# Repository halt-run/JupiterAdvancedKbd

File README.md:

# JupiterAdvancedKbd
Rep for the Jupiter Advanced Keyboard

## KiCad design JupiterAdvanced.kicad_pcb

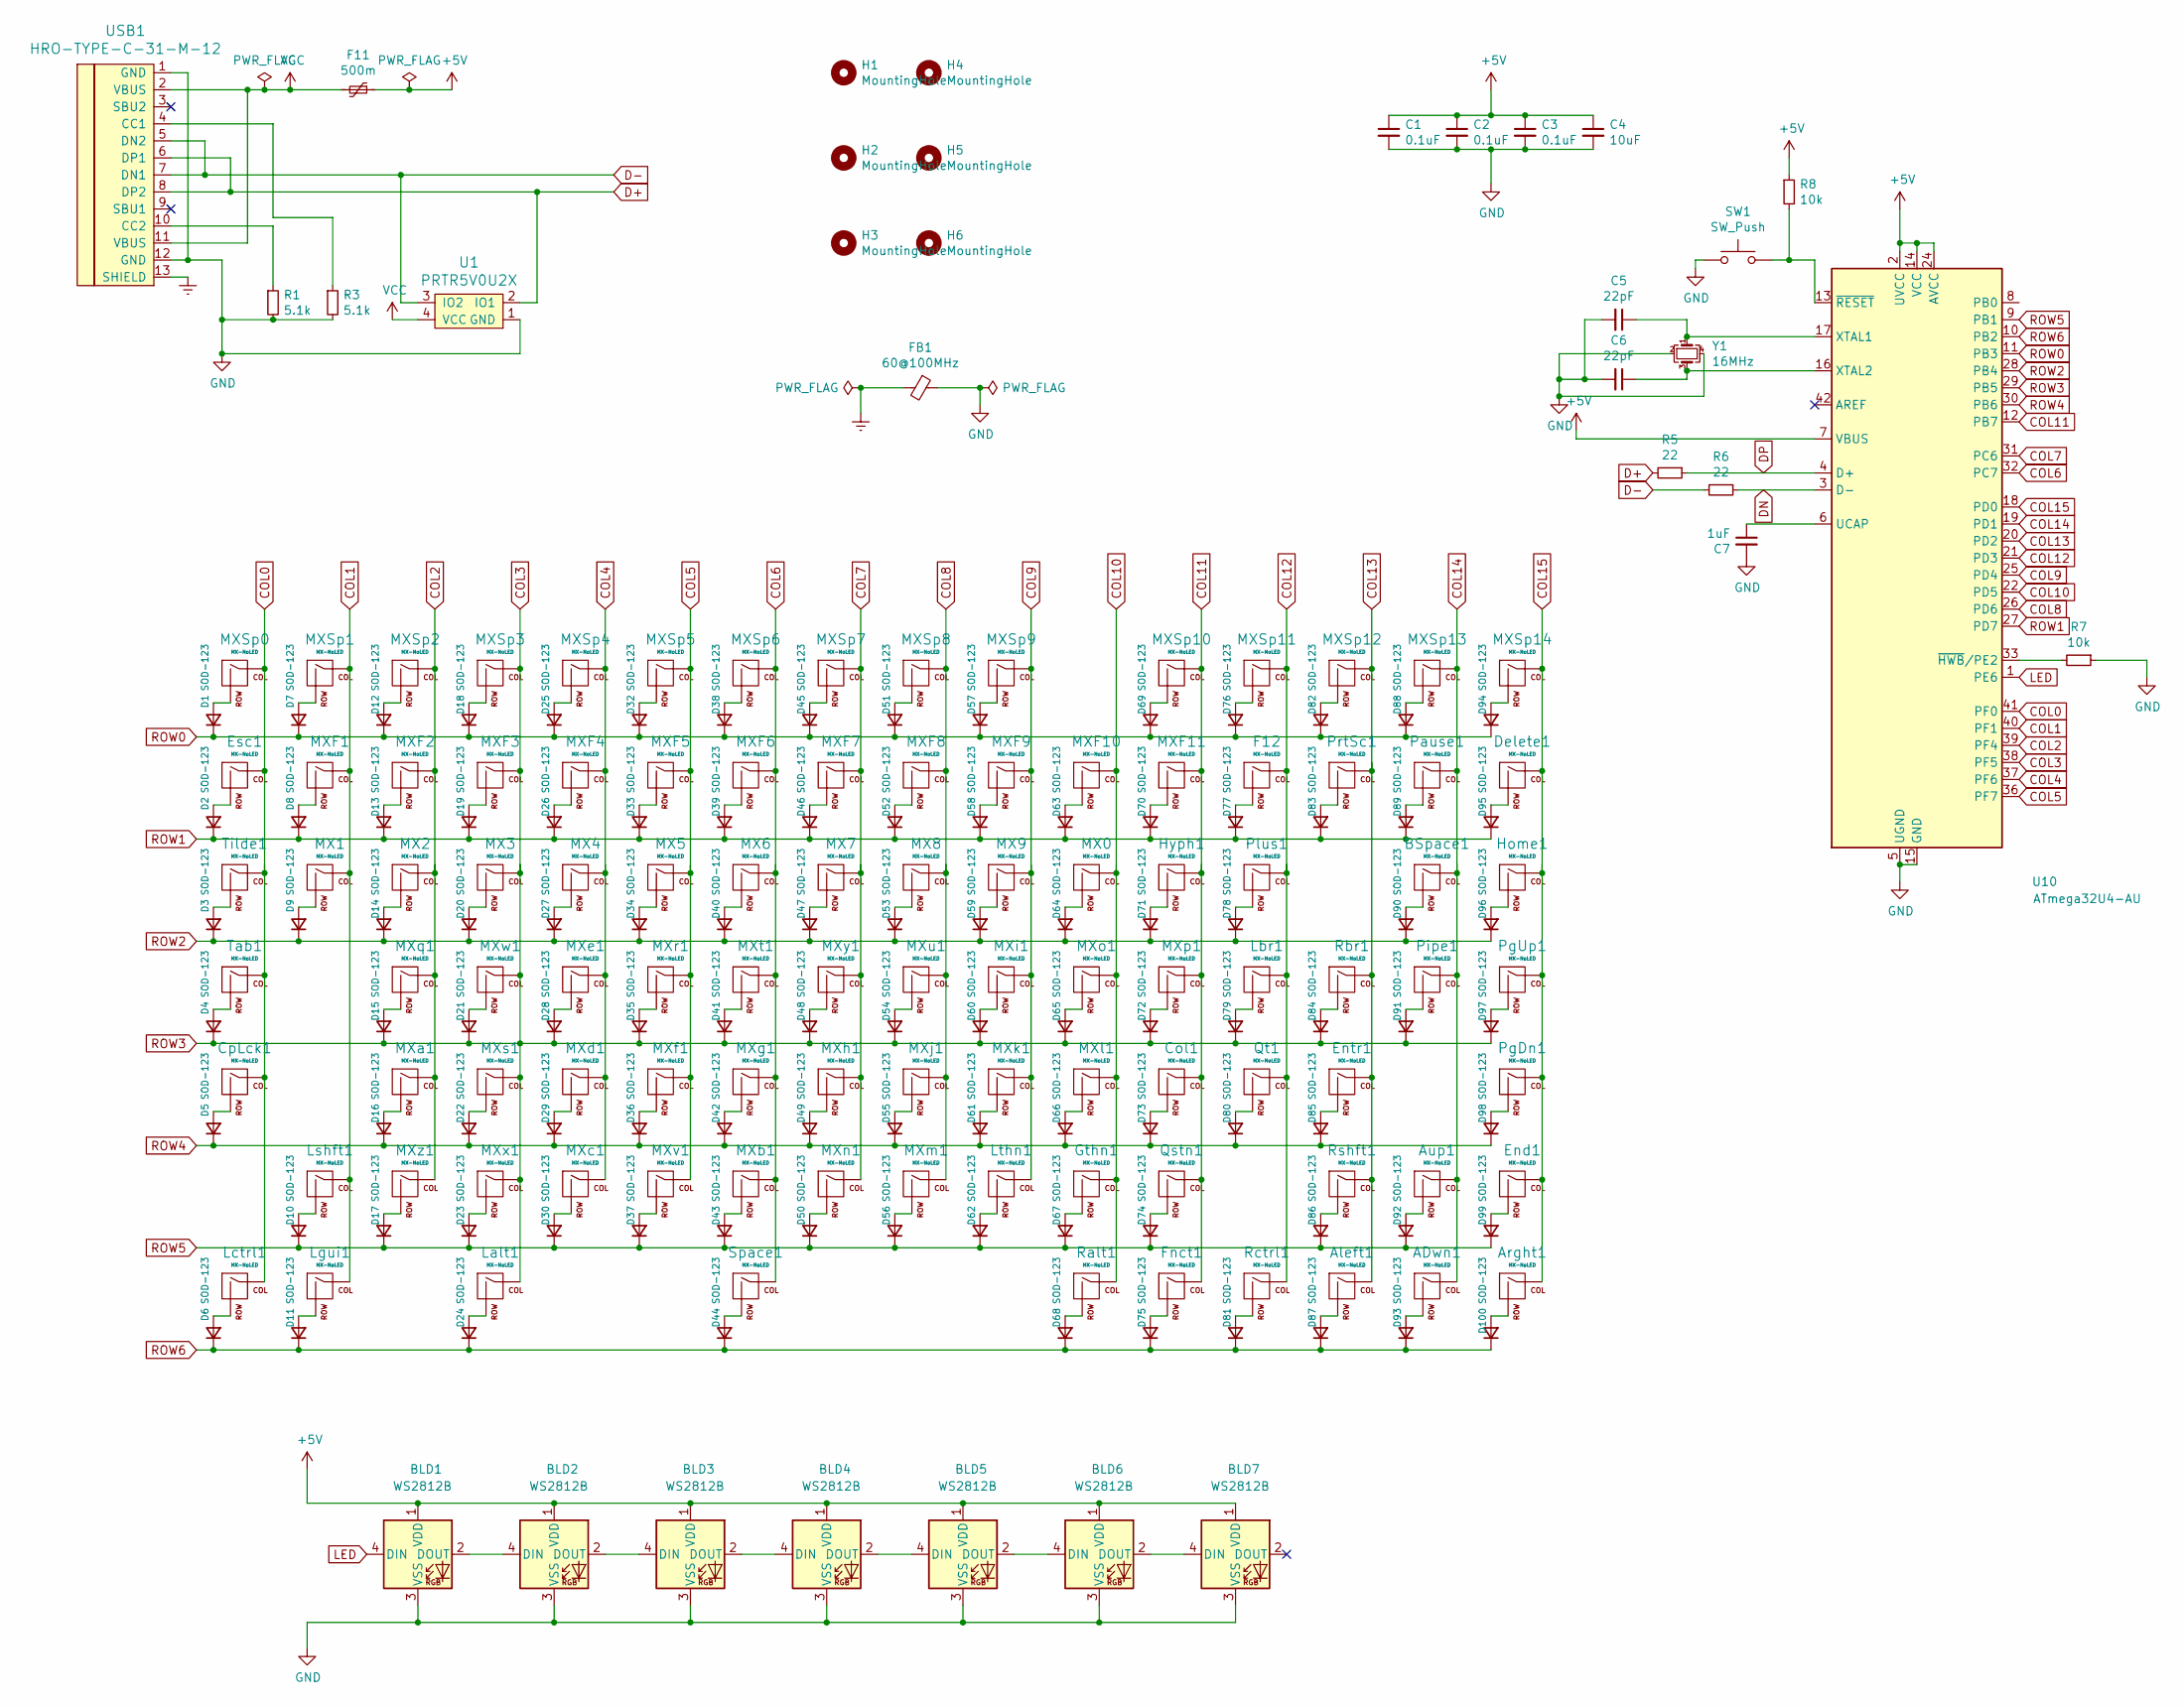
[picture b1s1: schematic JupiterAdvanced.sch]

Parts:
ADwn1: MX-NoLED; MXOnly-1U-NoLED
Aleft1: MX-NoLED; MXOnly-1U-NoLED
Arght1: MX-NoLED; MXOnly-1U-NoLED
Aup1: MX-NoLED; MXOnly-1U-NoLED
BLD1, BLD2, BLD3, BLD4, BLD5, BLD6, BLD7: WS2812B; LED_WS2812B_PLCC4_5.0x5.0mm_P3.2mm; LCSC C114586
BSpace1: MX-NoLED; MXOnly-2U-NoLED
C1, C2, C3: 0.1uF; C_0805_2012Metric; LCSC C1711
C4: 10uF; C_0805_2012Metric; LCSC C15850
C5, C6: 22pF; C_0805_2012Metric; LCSC C1804
C7: 1uF; C_0805_2012Metric; LCSC C28323
Col1: MX-NoLED; MXOnly-1U-NoLED
CpLck1: MX-NoLED; MXOnly-1.75U-NoLED
D1, D2, D3, D4, D5, D6, D7, D8, D9, D10, D11, D12, D13, D14, D15, D16, D17, D18, D19, D20, D21, D22, D23, D24, D25, D26, D27, D28, D29, D30, D32, D33, D34, D35, D36, D37, D38, D39, D40, D41, D42, D43, D44, D45, D46, D47, D48, D49, D50, D51, D52, D53, D54, D55, D56, D58, D59, D60, D61, D62, D63, D64, D65, D66, D67, D68, D69, D70, D71, D72, D73, D74, D75, D76, D77, D78, D79, D80, D81, D82, D83, D84, D85, D86, D87, D88, D89, D90, D91, D92, D93, D94, D95, D96, D97, D98, D99, D100: SOD-123; D_SOD-123; LCSC C81598
D57: SOD-123; D_SOD-123
Delete1: MX-NoLED; MXOnly-1U-NoLED
End1: MX-NoLED; MXOnly-1U-NoLED
Entr1: MX-NoLED; MXOnly-2.25U-NoLED
Esc1: MX-NoLED; MXOnly-1U-NoLED
F11: 500m; Fuse_1206_3216Metric; LCSC C163133
F12: MX-NoLED; MXOnly-1U-NoLED
FB1: 60@100MHz; L_1206_3216Metric; LCSC C131463
Fnct1: MX-NoLED; MXOnly-1U-NoLED
Gthn1: MX-NoLED; MXOnly-1U-NoLED
H1, H2, H3, H4, H5, H6: MountingHole; MountingHole_2.5mm
Home1: MX-NoLED; MXOnly-1U-NoLED
Hyph1: MX-NoLED; MXOnly-1U-NoLED
Lalt1: MX-NoLED; MXOnly-1.25U-NoLED
Lbr1: MX-NoLED; MXOnly-1U-NoLED
Lctrl1: MX-NoLED; MXOnly-1.25U-NoLED
Lgui1: MX-NoLED; MXOnly-1.25U-NoLED
Lshft1: MX-NoLED; MXOnly-2.25U-NoLED
Lthn1: MX-NoLED; MXOnly-1U-NoLED
MX0, MX1, MX2, MX3, MX4, MX5, MX6, MX7, MX8, MX9: MX-NoLED; MXOnly-1U-NoLED
MXF1, MXF2, MXF3, MXF4, MXF5, MXF6, MXF7, MXF8, MXF9, MXF10, MXF11: MX-NoLED; MXOnly-1U-NoLED
MXSp0, MXSp1, MXSp2, MXSp3, MXSp4, MXSp5, MXSp6, MXSp7, MXSp8, MXSp9, MXSp10, MXSp11, MXSp12, MXSp13, MXSp14: MX-NoLED; MXOnly-1U-NoLED
MXa1: MX-NoLED; MXOnly-1U-NoLED
MXb1: MX-NoLED; MXOnly-1U-NoLED
MXc1: MX-NoLED; MXOnly-1U-NoLED
MXd1: MX-NoLED; MXOnly-1U-NoLED
MXe1: MX-NoLED; MXOnly-1U-NoLED
MXf1: MX-NoLED; MXOnly-1U-NoLED
MXg1: MX-NoLED; MXOnly-1U-NoLED
MXh1: MX-NoLED; MXOnly-1U-NoLED
MXi1: MX-NoLED; MXOnly-1U-NoLED
MXj1: MX-NoLED; MXOnly-1U-NoLED
MXk1: MX-NoLED; MXOnly-1U-NoLED
MXl1: MX-NoLED; MXOnly-1U-NoLED
MXm1: MX-NoLED; MXOnly-1U-NoLED
MXn1: MX-NoLED; MXOnly-1U-NoLED
MXo1: MX-NoLED; MXOnly-1U-NoLED
MXp1: MX-NoLED; MXOnly-1U-NoLED
MXq1: MX-NoLED; MXOnly-1U-NoLED
MXr1: MX-NoLED; MXOnly-1U-NoLED
MXs1: MX-NoLED; MXOnly-1U-NoLED
MXt1: MX-NoLED; MXOnly-1U-NoLED
MXu1: MX-NoLED; MXOnly-1U-NoLED
MXv1: MX-NoLED; MXOnly-1U-NoLED
MXw1: MX-NoLED; MXOnly-1U-NoLED
MXx1: MX-NoLED; MXOnly-1U-NoLED
MXy1: MX-NoLED; MXOnly-1U-NoLED
MXz1: MX-NoLED; MXOnly-1U-NoLED
Pause1: MX-NoLED; MXOnly-1U-NoLED
PgDn1: MX-NoLED; MXOnly-1U-NoLED
PgUp1: MX-NoLED; MXOnly-1U-NoLED
Pipe1: MX-NoLED; MXOnly-1U-NoLED
Plus1: MX-NoLED; MXOnly-1U-NoLED
PrtSc1: MX-NoLED; MXOnly-1U-NoLED
Qstn1: MX-NoLED; MXOnly-1U-NoLED
Qt1: MX-NoLED; MXOnly-1U-NoLED
R1, R3: 5.1k; R_0805_2012Metric; LCSC C27834
R5, R6: 22; R_0805_2012Metric; LCSC C17561
R7, R8: 10k; R_0805_2012Metric; LCSC C17414
Ralt1: MX-NoLED; MXOnly-1U-NoLED
Rbr1: MX-NoLED; MXOnly-1U-NoLED
Rctrl1: MX-NoLED; MXOnly-1U-NoLED
Rshft1: MX-NoLED; MXOnly-1.75U-NoLED
SW1: SW_Push; SW_SPST_SKQG_WithoutStem; LCSC C202424
Space1: MX-NoLED; MXOnly-6.25U-NoLED
Tab1: MX-NoLED; MXOnly-1.5U-NoLED
Tilde1: MX-NoLED; MXOnly-1U-NoLED
U1: PRTR5V0U2X; SOT143B; LCSC C558444
U10: ATmega32U4-AU; TQFP-44_10x10mm_P0.8mm; LCSC C44854
USB1: HRO-TYPE-C-31-M-12; HRO-TYPE-C-31-M-12-Assembly; LCSC C165948
Y1: 16MHz; Crystal_SMD_3225-4Pin_3.2x2.5mm; LCSC C89379

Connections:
+5V: BLD1.1 (VDD), BLD2.1 (VDD), BLD3.1 (VDD), BLD4.1 (VDD), BLD5.1 (VDD), BLD6.1 (VDD), BLD7.1 (VDD), C1.1, C2.1, C3.1, C4.1, F11.1, R8.1, U10.2 (UVCC), U10.7 (VBUS), U10.14 (VCC), U10.24 (AVCC), U10.34 (VCC), U10.44 (AVCC)
COL0: CpLck1.1 (COL), Esc1.1 (COL), Lctrl1.1 (COL), MXSp0.1 (COL), Tab1.1 (COL), Tilde1.1 (COL), U10.41 (PF0)
COL1: Lgui1.1 (COL), Lshft1.1 (COL), MX1.1 (COL), MXF1.1 (COL), MXSp1.1 (COL), U10.40 (PF1)
COL2: MX2.1 (COL), MXF2.1 (COL), MXSp2.1 (COL), MXa1.1 (COL), MXq1.1 (COL), MXz1.1 (COL), U10.39 (PF4)
COL3: D4.1 (K), D15.1 (K), D21.1 (K), D28.1 (K), D35.1 (K), D41.1 (K), D48.1 (K), D54.1 (K), D60.1 (K), D65.1 (K), D72.1 (K), D79.1 (K), D84.1 (K), D91.1 (K), D97.1 (K), Lalt1.1 (COL), MX3.1 (COL), MXF3.1 (COL), MXSp3.1 (COL), MXs1.1 (COL), MXw1.1 (COL), MXx1.1 (COL), U10.29 (PB5), U10.38 (PF5)
COL4: MX4.1 (COL), MXF4.1 (COL), MXSp4.1 (COL), MXc1.1 (COL), MXd1.1 (COL), MXe1.1 (COL), U10.37 (PF6)
COL5: MX5.1 (COL), MXF5.1 (COL), MXSp5.1 (COL), MXf1.1 (COL), MXr1.1 (COL), MXv1.1 (COL), U10.36 (PF7)
COL6: MX6.1 (COL), MXF6.1 (COL), MXSp6.1 (COL), MXb1.1 (COL), MXg1.1 (COL), MXt1.1 (COL), Space1.1 (COL), U10.32 (PC7)
COL7: MX7.1 (COL), MXF7.1 (COL), MXSp7.1 (COL), MXh1.1 (COL), MXn1.1 (COL), MXy1.1 (COL), U10.31 (PC6)
COL8: MX8.1 (COL), MXF8.1 (COL), MXSp8.1 (COL), MXj1.1 (COL), MXm1.1 (COL), MXu1.1 (COL), U10.26 (PD6)
COL9: Lthn1.1 (COL), MX9.1 (COL), MXF9.1 (COL), MXSp9.1 (COL), MXi1.1 (COL), MXk1.1 (COL), U10.25 (PD4)
COL10: Gthn1.1 (COL), MX0.1 (COL), MXF10.1 (COL), MXl1.1 (COL), MXo1.1 (COL), Ralt1.1 (COL), U10.22 (PD5)
COL11: Col1.1 (COL), Fnct1.1 (COL), Hyph1.1 (COL), MXF11.1 (COL), MXSp10.1 (COL), MXp1.1 (COL), Qstn1.1 (COL), U10.12 (PB7)
COL12: F12.1 (COL), Lbr1.1 (COL), MXSp11.1 (COL), Plus1.1 (COL), Qt1.1 (COL), Rctrl1.1 (COL), U10.21 (PD3)
COL13: Aleft1.1 (COL), Entr1.1 (COL), MXSp12.1 (COL), PrtSc1.1 (COL), Rbr1.1 (COL), Rshft1.1 (COL), U10.20 (PD2)
COL14: ADwn1.1 (COL), Aup1.1 (COL), BSpace1.1 (COL), MXSp13.1 (COL), Pause1.1 (COL), Pipe1.1 (COL), U10.19 (PD1)
COL15: Arght1.1 (COL), Delete1.1 (COL), End1.1 (COL), Home1.1 (COL), MXSp14.1 (COL), PgDn1.1 (COL), PgUp1.1 (COL), U10.18 (PD0)
D+: R5.2, U1.2 (IO1), USB1.6 (DP1), USB1.8 (DP2)
D-: R6.2, U1.3 (IO2), USB1.5 (DN2), USB1.7 (DN1)
DN: R6.1, U10.3 (D-)
DP: R5.1, U10.4 (D+)
Earth: FB1.2, USB1.13 (SHIELD)
GND: BLD1.3 (VSS), BLD2.3 (VSS), BLD3.3 (VSS), BLD4.3 (VSS), BLD5.3 (VSS), BLD6.3 (VSS), BLD7.3 (VSS), C1.2, C2.2, C3.2, C4.2, C5.2, C6.2, C7.2, FB1.1, R1.2, R3.2, R7.1, SW1.1, U1.1 (GND), U10.5 (UGND), U10.15 (GND), U10.23 (GND), U10.35 (GND), U10.43 (GND), USB1.1 (GND), USB1.12 (GND), Y1.2, Y1.4
LED: BLD1.4 (DIN), U10.1 (PE6)
unnamed: ADwn1.2 (ROW), D93.2 (A)
unnamed: Aleft1.2 (ROW), D87.2 (A)
unnamed: Arght1.2 (ROW), D100.2 (A)
unnamed: Aup1.2 (ROW), D92.2 (A)
unnamed: BLD1.2 (DOUT), BLD2.4 (DIN)
unnamed: BLD2.2 (DOUT), BLD3.4 (DIN)
unnamed: BLD3.2 (DOUT), BLD4.4 (DIN)
unnamed: BLD4.2 (DOUT), BLD5.4 (DIN)
unnamed: BLD5.2 (DOUT), BLD6.4 (DIN)
unnamed: BLD6.2 (DOUT), BLD7.4 (DIN)
unnamed: BSpace1.2 (ROW), D90.2 (A)
unnamed: C5.1, U10.17 (XTAL1), Y1.1
unnamed: C6.1, U10.16 (XTAL2), Y1.3
unnamed: C7.1, U10.6 (UCAP)
unnamed: Col1.2 (ROW), D73.2 (A)
unnamed: CpLck1.2 (ROW), D5.2 (A)
unnamed: D1.2 (A), MXSp0.2 (ROW)
unnamed: D2.2 (A), Esc1.2 (ROW)
unnamed: D3.2 (A), Tilde1.2 (ROW)
unnamed: D4.2 (A), Tab1.2 (ROW)
unnamed: D6.2 (A), Lctrl1.2 (ROW)
unnamed: D7.2 (A), MXSp1.2 (ROW)
unnamed: D8.2 (A), MXF1.2 (ROW)
unnamed: D9.2 (A), MX1.2 (ROW)
unnamed: D10.2 (A), Lshft1.2 (ROW)
unnamed: D11.2 (A), Lgui1.2 (ROW)
unnamed: D12.2 (A), MXSp2.2 (ROW)
unnamed: D13.2 (A), MXF2.2 (ROW)
unnamed: D14.2 (A), MX2.2 (ROW)
unnamed: D15.2 (A), MXq1.2 (ROW)
unnamed: D16.2 (A), MXa1.2 (ROW)
unnamed: D17.2 (A), MXz1.2 (ROW)
unnamed: D18.2 (A), MXSp3.2 (ROW)
unnamed: D19.2 (A), MXF3.2 (ROW)
unnamed: D20.2 (A), MX3.2 (ROW)
unnamed: D21.2 (A), MXw1.2 (ROW)
unnamed: D22.2 (A), MXs1.2 (ROW)
unnamed: D23.2 (A), MXx1.2 (ROW)
unnamed: D24.2 (A), Lalt1.2 (ROW)
unnamed: D25.2 (A), MXSp4.2 (ROW)
unnamed: D26.2 (A), MXF4.2 (ROW)
unnamed: D27.2 (A), MX4.2 (ROW)
unnamed: D28.2 (A), MXe1.2 (ROW)
unnamed: D29.2 (A), MXd1.2 (ROW)
unnamed: D30.2 (A), MXc1.2 (ROW)
unnamed: D32.2 (A), MXSp5.2 (ROW)
unnamed: D33.2 (A), MXF5.2 (ROW)
unnamed: D34.2 (A), MX5.2 (ROW)
unnamed: D35.2 (A), MXr1.2 (ROW)
unnamed: D36.2 (A), MXf1.2 (ROW)
unnamed: D37.2 (A), MXv1.2 (ROW)
unnamed: D38.2 (A), MXSp6.2 (ROW)
unnamed: D39.2 (A), MXF6.2 (ROW)
unnamed: D40.2 (A), MX6.2 (ROW)
unnamed: D41.2 (A), MXt1.2 (ROW)
unnamed: D42.2 (A), MXg1.2 (ROW)
unnamed: D43.2 (A), MXb1.2 (ROW)
unnamed: D44.2 (A), Space1.2 (ROW)
unnamed: D45.2 (A), MXSp7.2 (ROW)
unnamed: D46.2 (A), MXF7.2 (ROW)
unnamed: D47.2 (A), MX7.2 (ROW)
unnamed: D48.2 (A), MXy1.2 (ROW)
unnamed: D49.2 (A), MXh1.2 (ROW)
unnamed: D50.2 (A), MXn1.2 (ROW)
unnamed: D51.2 (A), MXSp8.2 (ROW)
unnamed: D52.2 (A), MXF8.2 (ROW)
unnamed: D53.2 (A), MX8.2 (ROW)
unnamed: D54.2 (A), MXu1.2 (ROW)
unnamed: D55.2 (A), MXj1.2 (ROW)
unnamed: D56.2 (A), MXm1.2 (ROW)
unnamed: D57.2 (A), MXSp9.2 (ROW)
unnamed: D58.2 (A), MXF9.2 (ROW)
unnamed: D59.2 (A), MX9.2 (ROW)
unnamed: D60.2 (A), MXi1.2 (ROW)
unnamed: D61.2 (A), MXk1.2 (ROW)
unnamed: D62.2 (A), Lthn1.2 (ROW)
unnamed: D63.2 (A), MXF10.2 (ROW)
unnamed: D64.2 (A), MX0.2 (ROW)
unnamed: D65.2 (A), MXo1.2 (ROW)
unnamed: D66.2 (A), MXl1.2 (ROW)
unnamed: D67.2 (A), Gthn1.2 (ROW)
unnamed: D68.2 (A), Ralt1.2 (ROW)
unnamed: D69.2 (A), MXSp10.2 (ROW)
unnamed: D70.2 (A), MXF11.2 (ROW)
unnamed: D71.2 (A), Hyph1.2 (ROW)
unnamed: D72.2 (A), MXp1.2 (ROW)
unnamed: D74.2 (A), Qstn1.2 (ROW)
unnamed: D75.2 (A), Fnct1.2 (ROW)
unnamed: D76.2 (A), MXSp11.2 (ROW)
unnamed: D77.2 (A), F12.2 (ROW)
unnamed: D78.2 (A), Plus1.2 (ROW)
unnamed: D79.2 (A), Lbr1.2 (ROW)
unnamed: D80.2 (A), Qt1.2 (ROW)
unnamed: D81.2 (A), Rctrl1.2 (ROW)
unnamed: D82.2 (A), MXSp12.2 (ROW)
unnamed: D83.2 (A), PrtSc1.2 (ROW)
unnamed: D84.2 (A), Rbr1.2 (ROW)
unnamed: D85.2 (A), Entr1.2 (ROW)
unnamed: D86.2 (A), Rshft1.2 (ROW)
unnamed: D88.2 (A), MXSp13.2 (ROW)
unnamed: D89.2 (A), Pause1.2 (ROW)
unnamed: D91.2 (A), Pipe1.2 (ROW)
unnamed: D94.2 (A), MXSp14.2 (ROW)
unnamed: D95.2 (A), Delete1.2 (ROW)
unnamed: D96.2 (A), Home1.2 (ROW)
unnamed: D97.2 (A), PgUp1.2 (ROW)
unnamed: D98.2 (A), PgDn1.2 (ROW)
unnamed: D99.2 (A), End1.2 (ROW)
unnamed: R1.1, USB1.10 (CC2)
unnamed: R3.1, USB1.4 (CC1)
unnamed: R7.2, U10.33 (~HWB~/PE2)
unnamed: R8.2, SW1.2, U10.13 (~RESET)
ROW0: D1.1 (K), D7.1 (K), D12.1 (K), D18.1 (K), D25.1 (K), D32.1 (K), D38.1 (K), D45.1 (K), D51.1 (K), D57.1 (K), D69.1 (K), D76.1 (K), D82.1 (K), D88.1 (K), D94.1 (K), U10.11 (PB3)
ROW1: D2.1 (K), D8.1 (K), D13.1 (K), D19.1 (K), D26.1 (K), D33.1 (K), D39.1 (K), D46.1 (K), D52.1 (K), D58.1 (K), D63.1 (K), D70.1 (K), D77.1 (K), D83.1 (K), D89.1 (K), D95.1 (K), U10.27 (PD7)
ROW2: D3.1 (K), D9.1 (K), D14.1 (K), D20.1 (K), D27.1 (K), D34.1 (K), D40.1 (K), D47.1 (K), D53.1 (K), D59.1 (K), D64.1 (K), D71.1 (K), D78.1 (K), D90.1 (K), D96.1 (K), U10.28 (PB4)
ROW4: D5.1 (K), D16.1 (K), D22.1 (K), D29.1 (K), D36.1 (K), D42.1 (K), D49.1 (K), D55.1 (K), D61.1 (K), D66.1 (K), D73.1 (K), D80.1 (K), D85.1 (K), D98.1 (K), U10.30 (PB6)
ROW5: D10.1 (K), D17.1 (K), D23.1 (K), D30.1 (K), D37.1 (K), D43.1 (K), D50.1 (K), D56.1 (K), D62.1 (K), D67.1 (K), D74.1 (K), D86.1 (K), D92.1 (K), D99.1 (K), U10.9 (PB1)
ROW6: D6.1 (K), D11.1 (K), D24.1 (K), D44.1 (K), D68.1 (K), D75.1 (K), D81.1 (K), D87.1 (K), D93.1 (K), D100.1 (K), U10.10 (PB2)
VCC: F11.2, U1.4 (VCC), USB1.2 (VBUS), USB1.11 (VBUS)

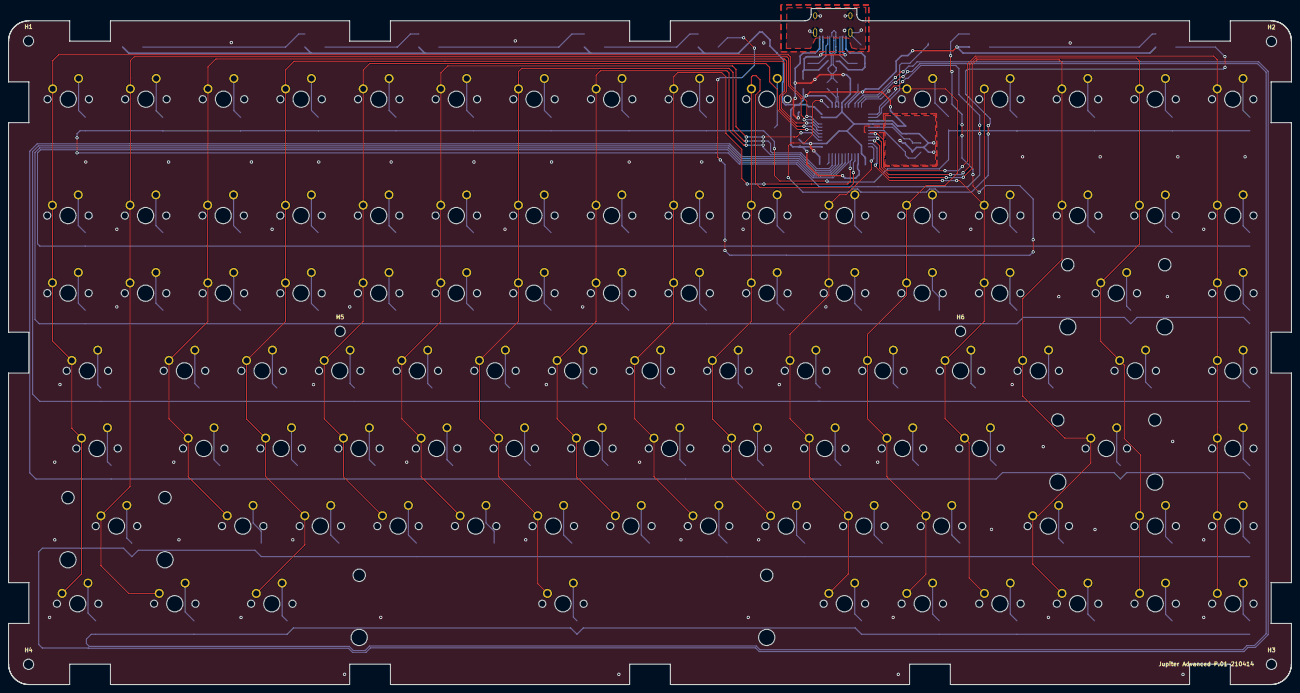
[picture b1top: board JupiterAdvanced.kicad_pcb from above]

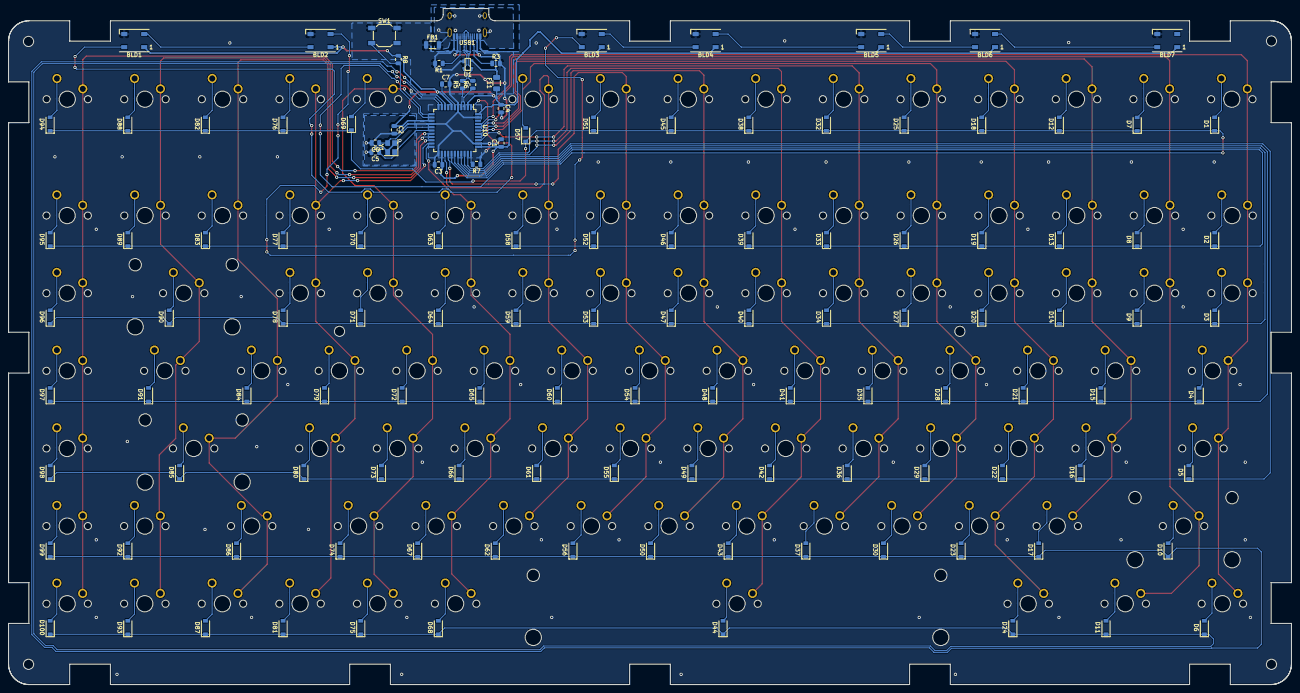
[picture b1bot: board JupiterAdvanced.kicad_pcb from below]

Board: 2 copper layers, 314.8 x 165.9 mm, 231 parts (126 on the bottom side), 143 nets.

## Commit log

2021-04-11 Added submodles
2021-04-11 Starting point for the KiCad Repo
2021-04-11 MCU added
2021-04-11 MCU schematic zone completed
2021-04-11 USB C Schematic Zone added
2021-04-11 USB C Schematic Zone completed
2021-04-11 Key Switch Matrix added
2021-04-11 Layout and Plate files added
2021-04-11 Key Switch Matrix completed
2021-04-11 Key Switch Matrix Row numbering fixed
2021-04-11 Key Switch labeling complete
2021-04-11 All footprints added
2021-04-11 PCB Switch locations complete
2021-04-11 All diodes placed on PCB (no routes)
2021-04-11 All Diodes moved to B.cu
2021-04-11 Design Notes.txt added
2021-04-11 LastOfDay - Cutout and Switch alignment still unfinished.
2021-04-12 DXF file to test switch location on PCB added.
2021-04-12 All cutouts, switch locations and diodes aligned
2021-04-12 Cleaned up USB C connector resistors
2021-04-12 Columns Routed. Working on the USB C connector routing.
2021-04-12 Routing work
    USB connector and pairs routed. Rows 1-6 complete. Row 0 still needs work
2021-04-12 Crystal and most decCaps done.
    Still haven't routed the VCC lines from the USB connector.
2021-04-13 Component net complete
2021-04-13 Files added
2021-04-13 Key Matrix Connected
2021-04-14 All routings and DRC cleared
2021-04-14 updated labels
2021-04-14 Added gerber files
2021-04-15 Minor fixes
2021-04-15 Gerber Files updated, Drill holes added
2021-04-15 Gerber files updated
2021-04-15 Drill holes aligned with board
2021-04-16 Added switchplate files for manufacturing
2021-04-18 LCSC added to USB system
2021-04-18 LCSC parts numbers added
2021-04-18 Ferret Bead added on USB Ground
2021-04-19 Mounting holes updated
2021-04-19 ATMega32u4 MCU added
2021-04-19 Matrix reconnect, still missing some pins.
2021-04-19 removed surplus via
2021-04-20 Rerouting for atmega32u4 complete
    and its a complete mess...
2021-04-20 Push switch updated for JLCPCB
2021-04-20 JLCPCB Order SMT0210420181311
    SMT0210420181311-3234210A
2021-04-21 Cleaning up files
2021-04-21 Added acryllic bottom plate files
2021-04-22 BasketCasePrototypeStep added
2021-04-23 Further work on the case files
2021-04-24 Case design updated
2021-04-28 Firmware and drawings for case added
2021-05-03 Rerouted matrix nets to create space for PCB mounting holes
2021-05-05 Cutouts in PCB created, USB port moved to protrude
2021-05-06 Updates to various Case Files
2021-05-07 FW Updated
2021-05-10 Added updated Step Files for Case
2021-05-10 Case work
2021-05-12 Updating PCB data
2021-05-12 JLCPCB W202105121404401
2021-05-16 Minor adjustments
2021-05-16 UnderGlow added, not yet routed
2021-05-16 GND Pours added
2021-05-16 Push Switch updated, Underglow LED work started
2021-05-16 Underglow Work continued
2021-05-16 Underglow Routing Complete
    Underglow routing is complete, but must be reworked for routing esthetics.
2021-05-26 Switch plate files updated
2021-06-20 BasketCaseTopPlate added
2021-06-21 top plate work basket case
2021-06-21 Basket case files updated
